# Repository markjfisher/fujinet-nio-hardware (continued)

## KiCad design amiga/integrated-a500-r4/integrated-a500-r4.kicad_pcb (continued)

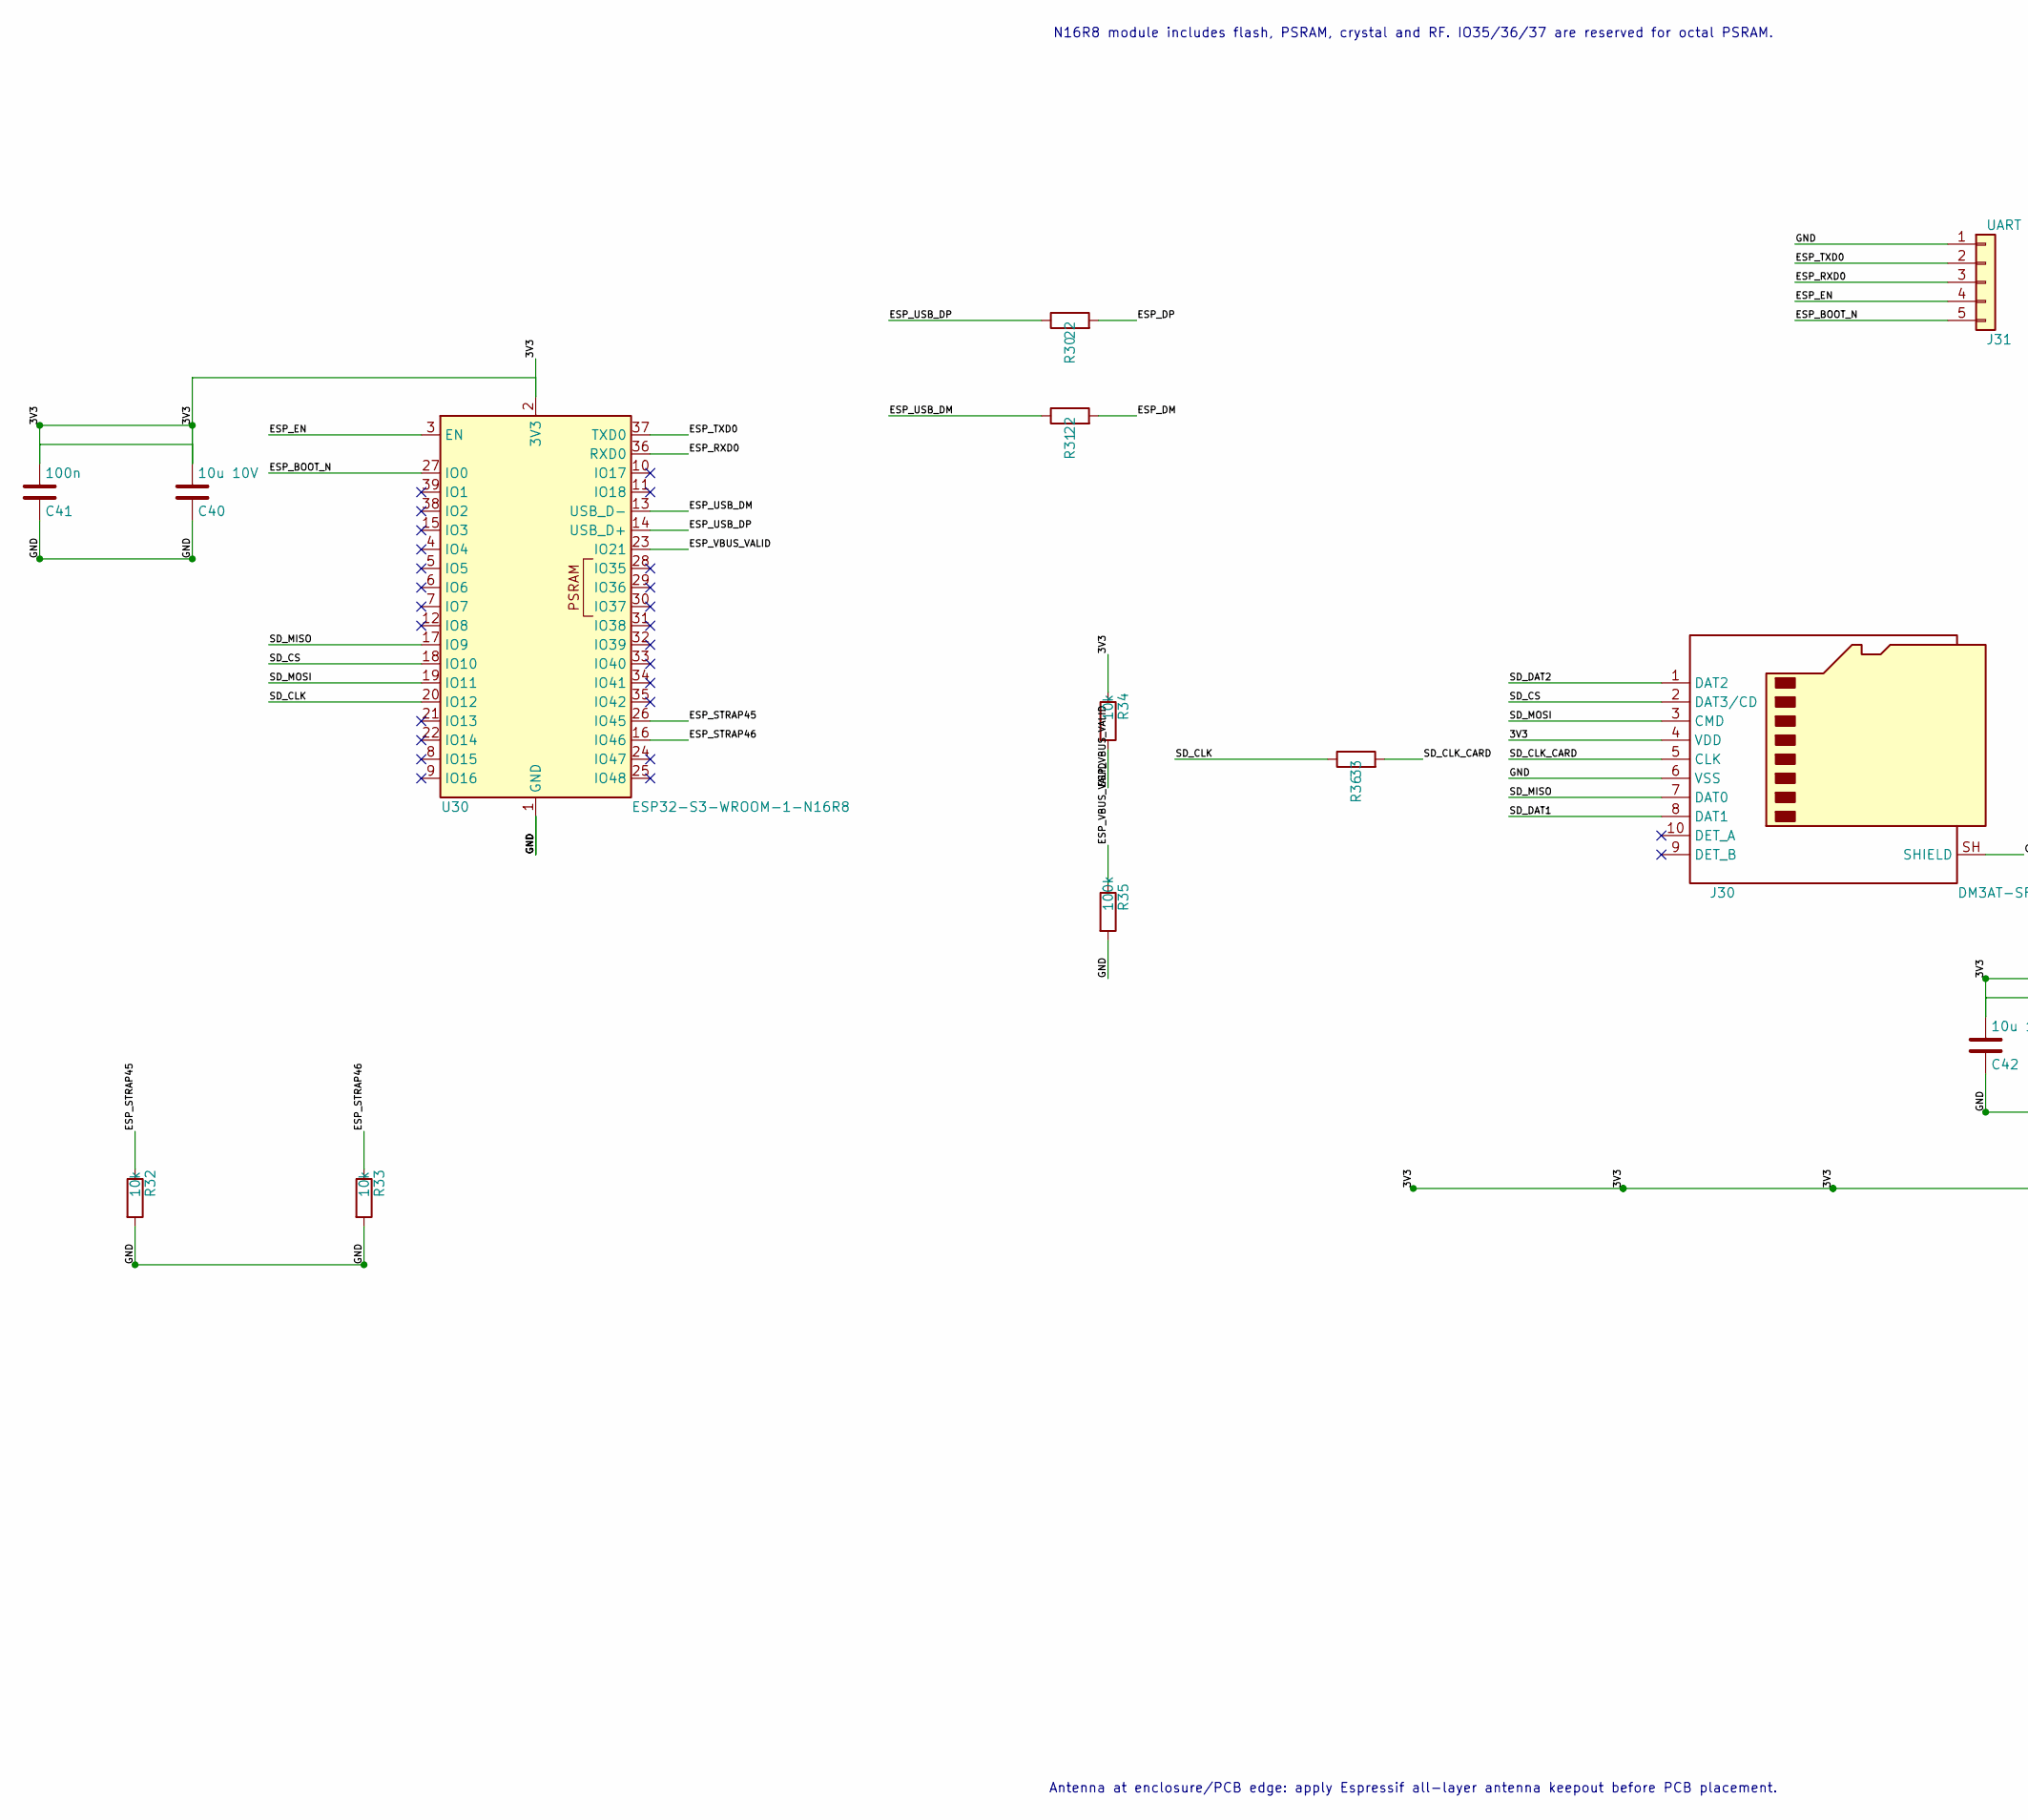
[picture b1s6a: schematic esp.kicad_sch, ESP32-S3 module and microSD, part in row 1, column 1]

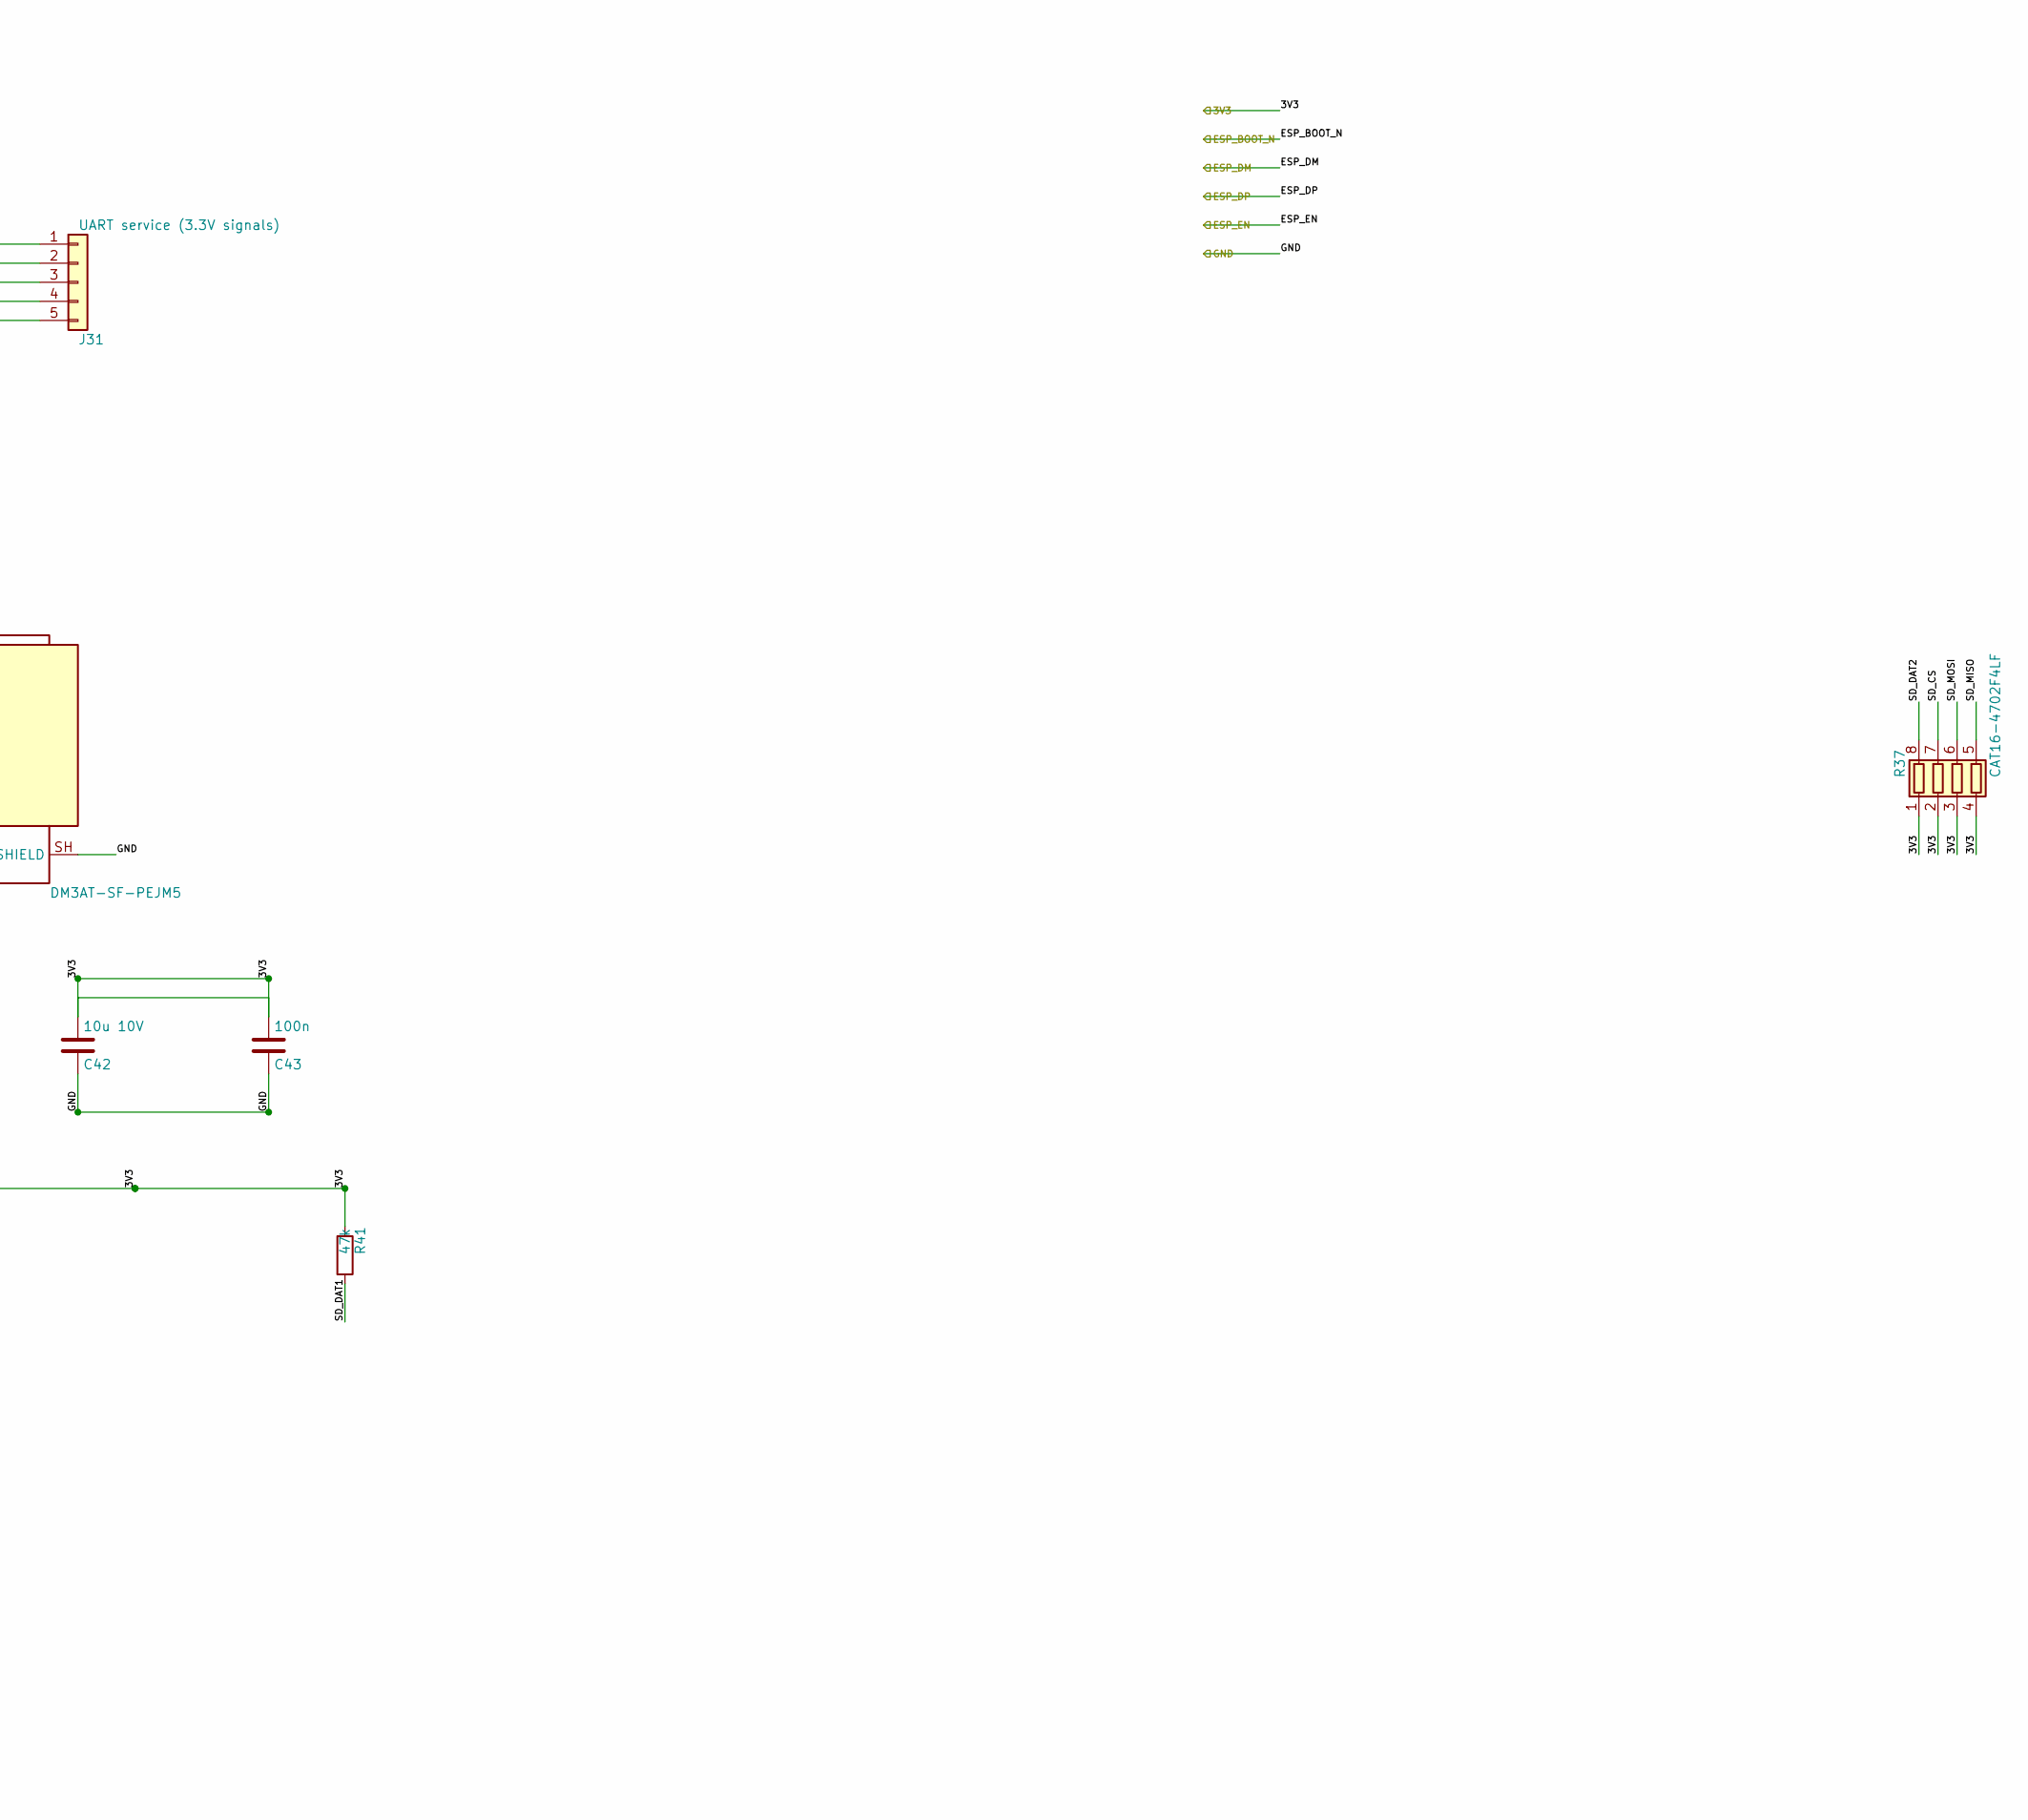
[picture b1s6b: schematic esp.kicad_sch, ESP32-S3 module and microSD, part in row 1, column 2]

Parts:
C40, C42: 10u 10V; C_0603_1608Metric
C41, C43: 100n; C_0603_1608Metric
J30: DM3AT-SF-PEJM5; microSD_HC_Hirose_DM3AT-SF-PEJM5
J31: UART service (3.3V signals); PinHeader_1x05_P2.54mm_Vertical
R30, R31: 22; R_0603_1608Metric
R32, R33, R34: 10k; R_0603_1608Metric
R35: 100k; R_0603_1608Metric
R36: 33; R_0603_1608Metric
R37: CAT16-4702F4LF; R_Array_Concave_4x0603
R41: 47k; R_0603_1608Metric
U30: ESP32-S3-WROOM-1-N16R8; ESP32-S3-WROOM-1

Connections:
/3V3: C40.1, C41.1, C42.1, C43.1, J30.4 (VDD), R34.1, R37.1 (R1.1), R37.2 (R2.1), R37.3 (R3.1), R37.4 (R4.1), R41.1, U30.2 (3V3); also elsewhere on the board
/ESP32-S3 module and microSD/ESP_RXD0: J31.3, U30.36 (RXD0)
/ESP32-S3 module and microSD/ESP_STRAP45: R32.1, U30.26 (IO45)
/ESP32-S3 module and microSD/ESP_STRAP46: R33.1, U30.16 (IO46)
/ESP32-S3 module and microSD/ESP_TXD0: J31.2, U30.37 (TXD0)
/ESP32-S3 module and microSD/ESP_USB_DM: R31.1, U30.13 (USB_D-)
/ESP32-S3 module and microSD/ESP_USB_DP: R30.1, U30.14 (USB_D+)
/ESP32-S3 module and microSD/ESP_VBUS_VALID: R34.2, R35.1, U30.23 (IO21)
/ESP32-S3 module and microSD/SD_CLK: R36.1, U30.20 (IO12)
/ESP32-S3 module and microSD/SD_CLK_CARD: J30.5 (CLK), R36.2
/ESP32-S3 module and microSD/SD_CS: J30.2 (DAT3/CD), R37.7 (R2.2), U30.18 (IO10)
/ESP32-S3 module and microSD/SD_DAT1: J30.8 (DAT1), R41.2
/ESP32-S3 module and microSD/SD_DAT2: J30.1 (DAT2), R37.8 (R1.2)
/ESP32-S3 module and microSD/SD_MISO: J30.7 (DAT0), R37.5 (R4.2), U30.17 (IO9)
/ESP32-S3 module and microSD/SD_MOSI: J30.3 (CMD), R37.6 (R3.2), U30.19 (IO11)
/ESP_BOOT_N: J31.5, U30.27 (IO0); also elsewhere on the board
/ESP_DM: R31.2; also elsewhere on the board
/ESP_DP: R30.2; also elsewhere on the board
/ESP_EN: J31.4, U30.3 (EN); also elsewhere on the board

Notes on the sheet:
N16R8 module includes flash, PSRAM, crystal and RF. IO35/36/37 are reserved for octal PSRAM.
Antenna at enclosure/PCB edge: apply Espressif all-layer antenna keepout before PCB placement.

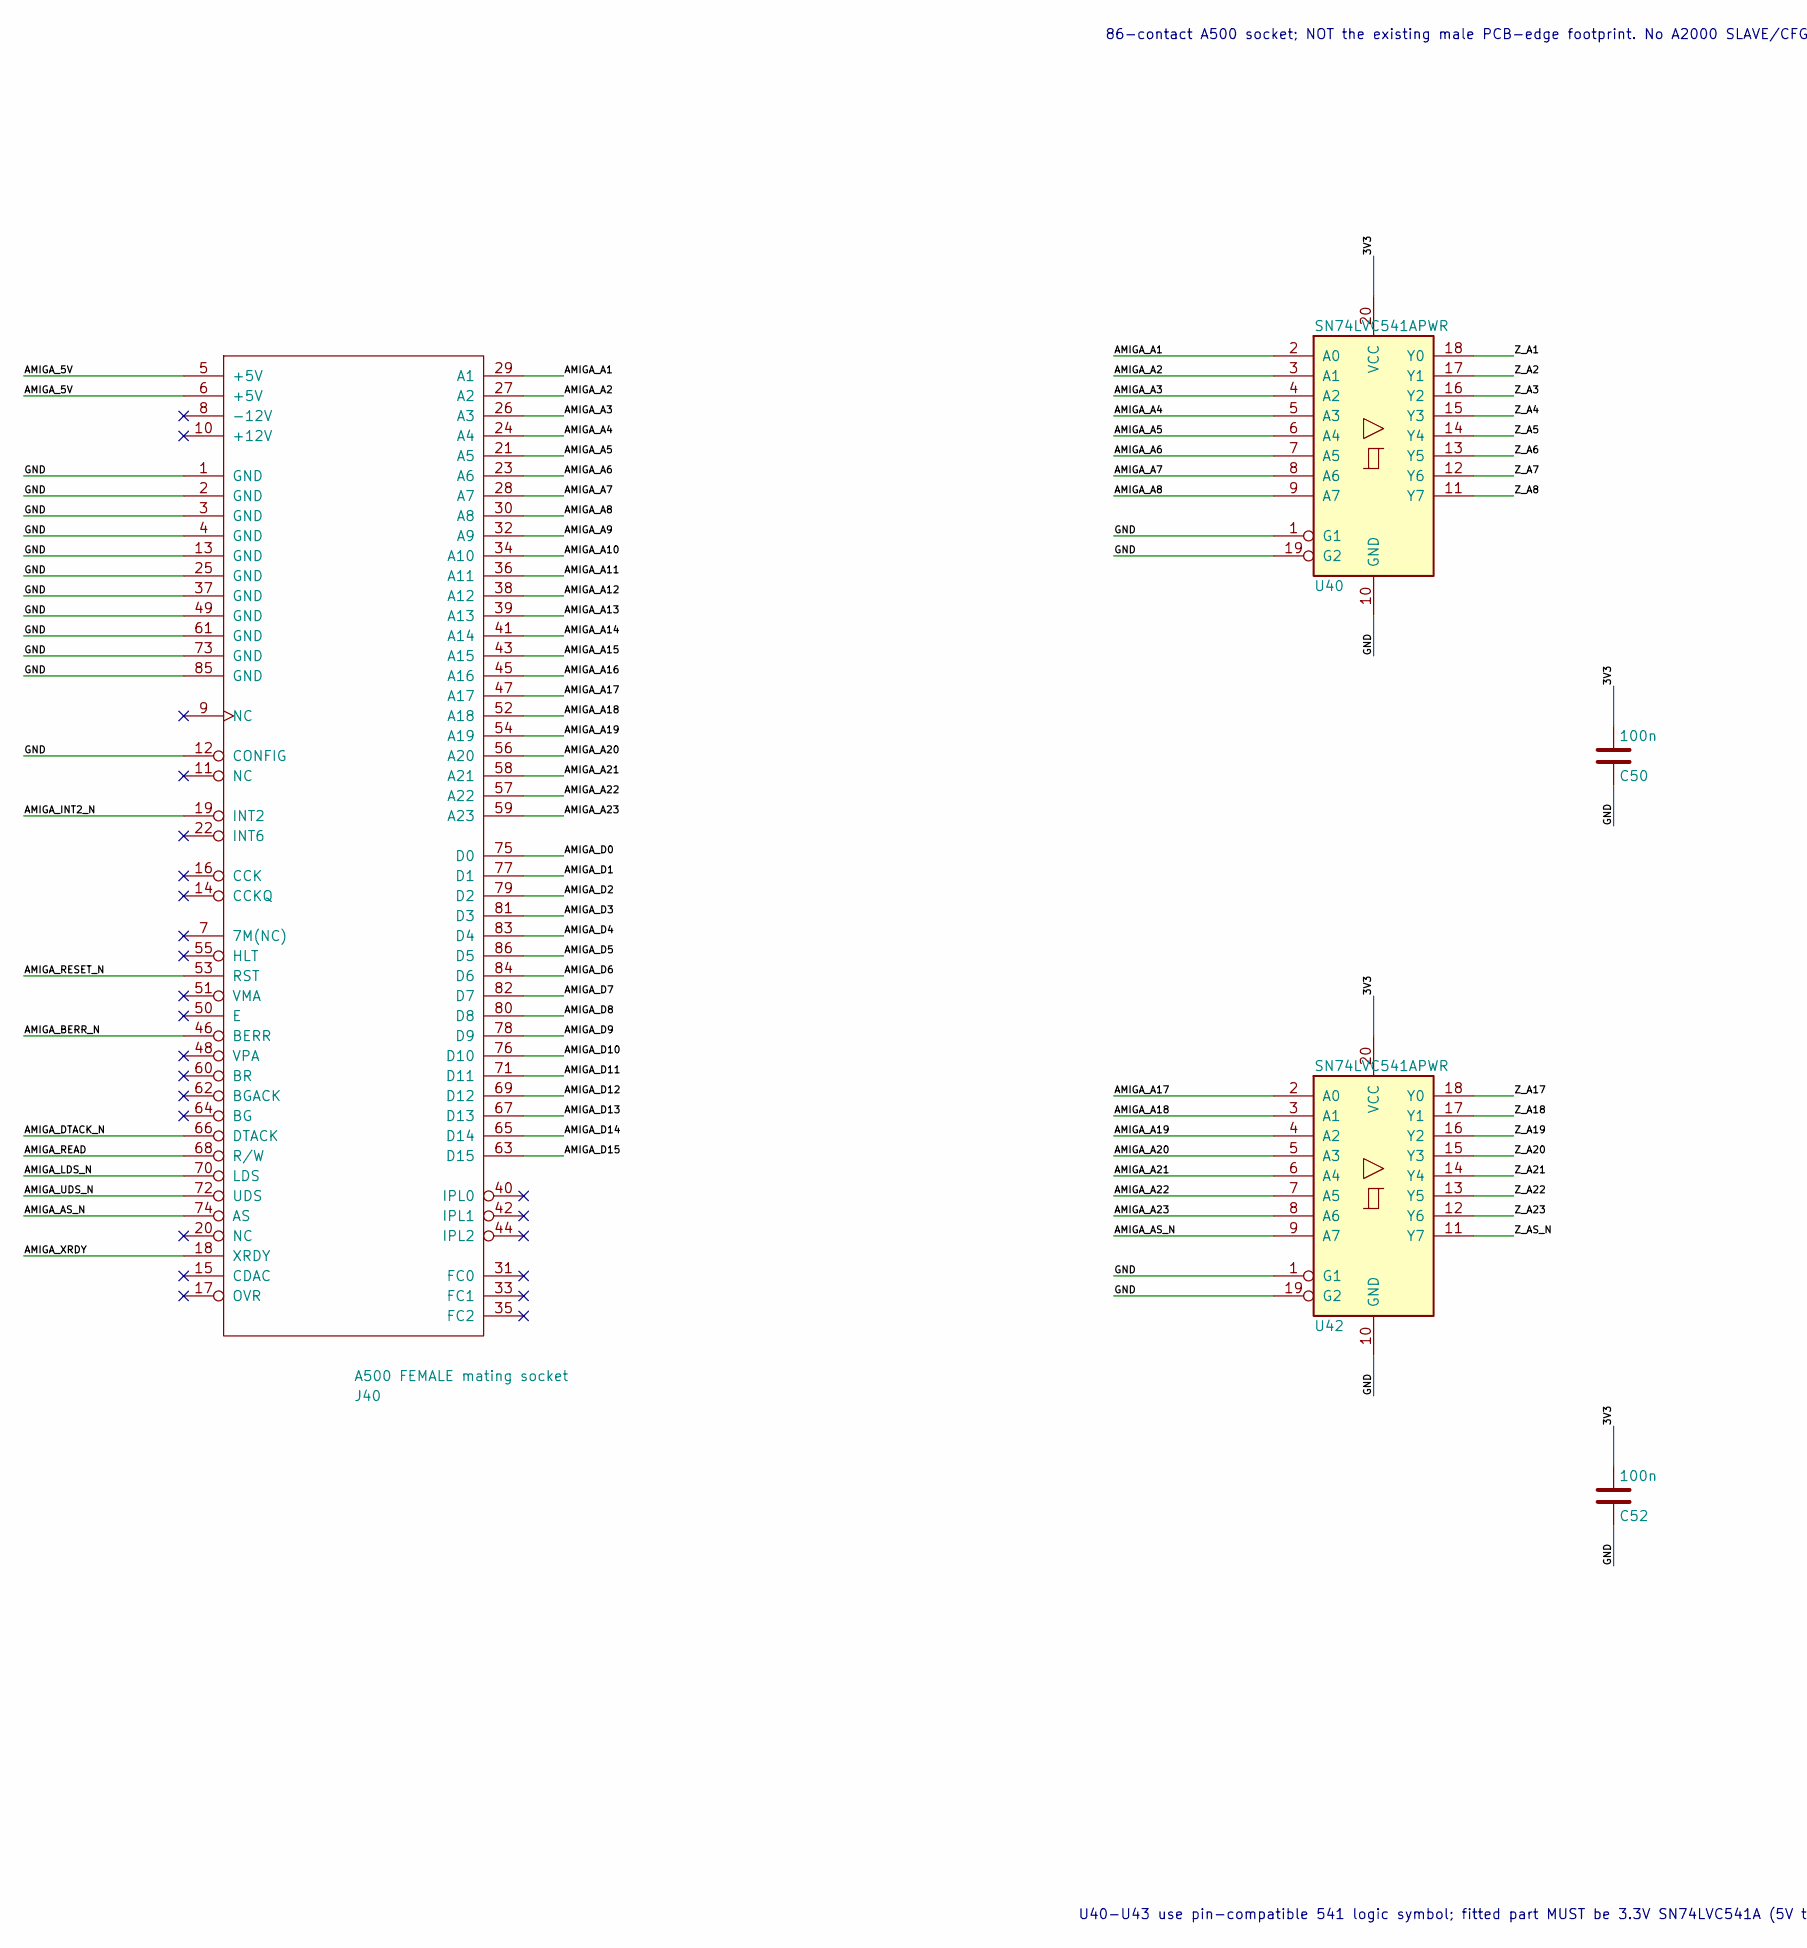
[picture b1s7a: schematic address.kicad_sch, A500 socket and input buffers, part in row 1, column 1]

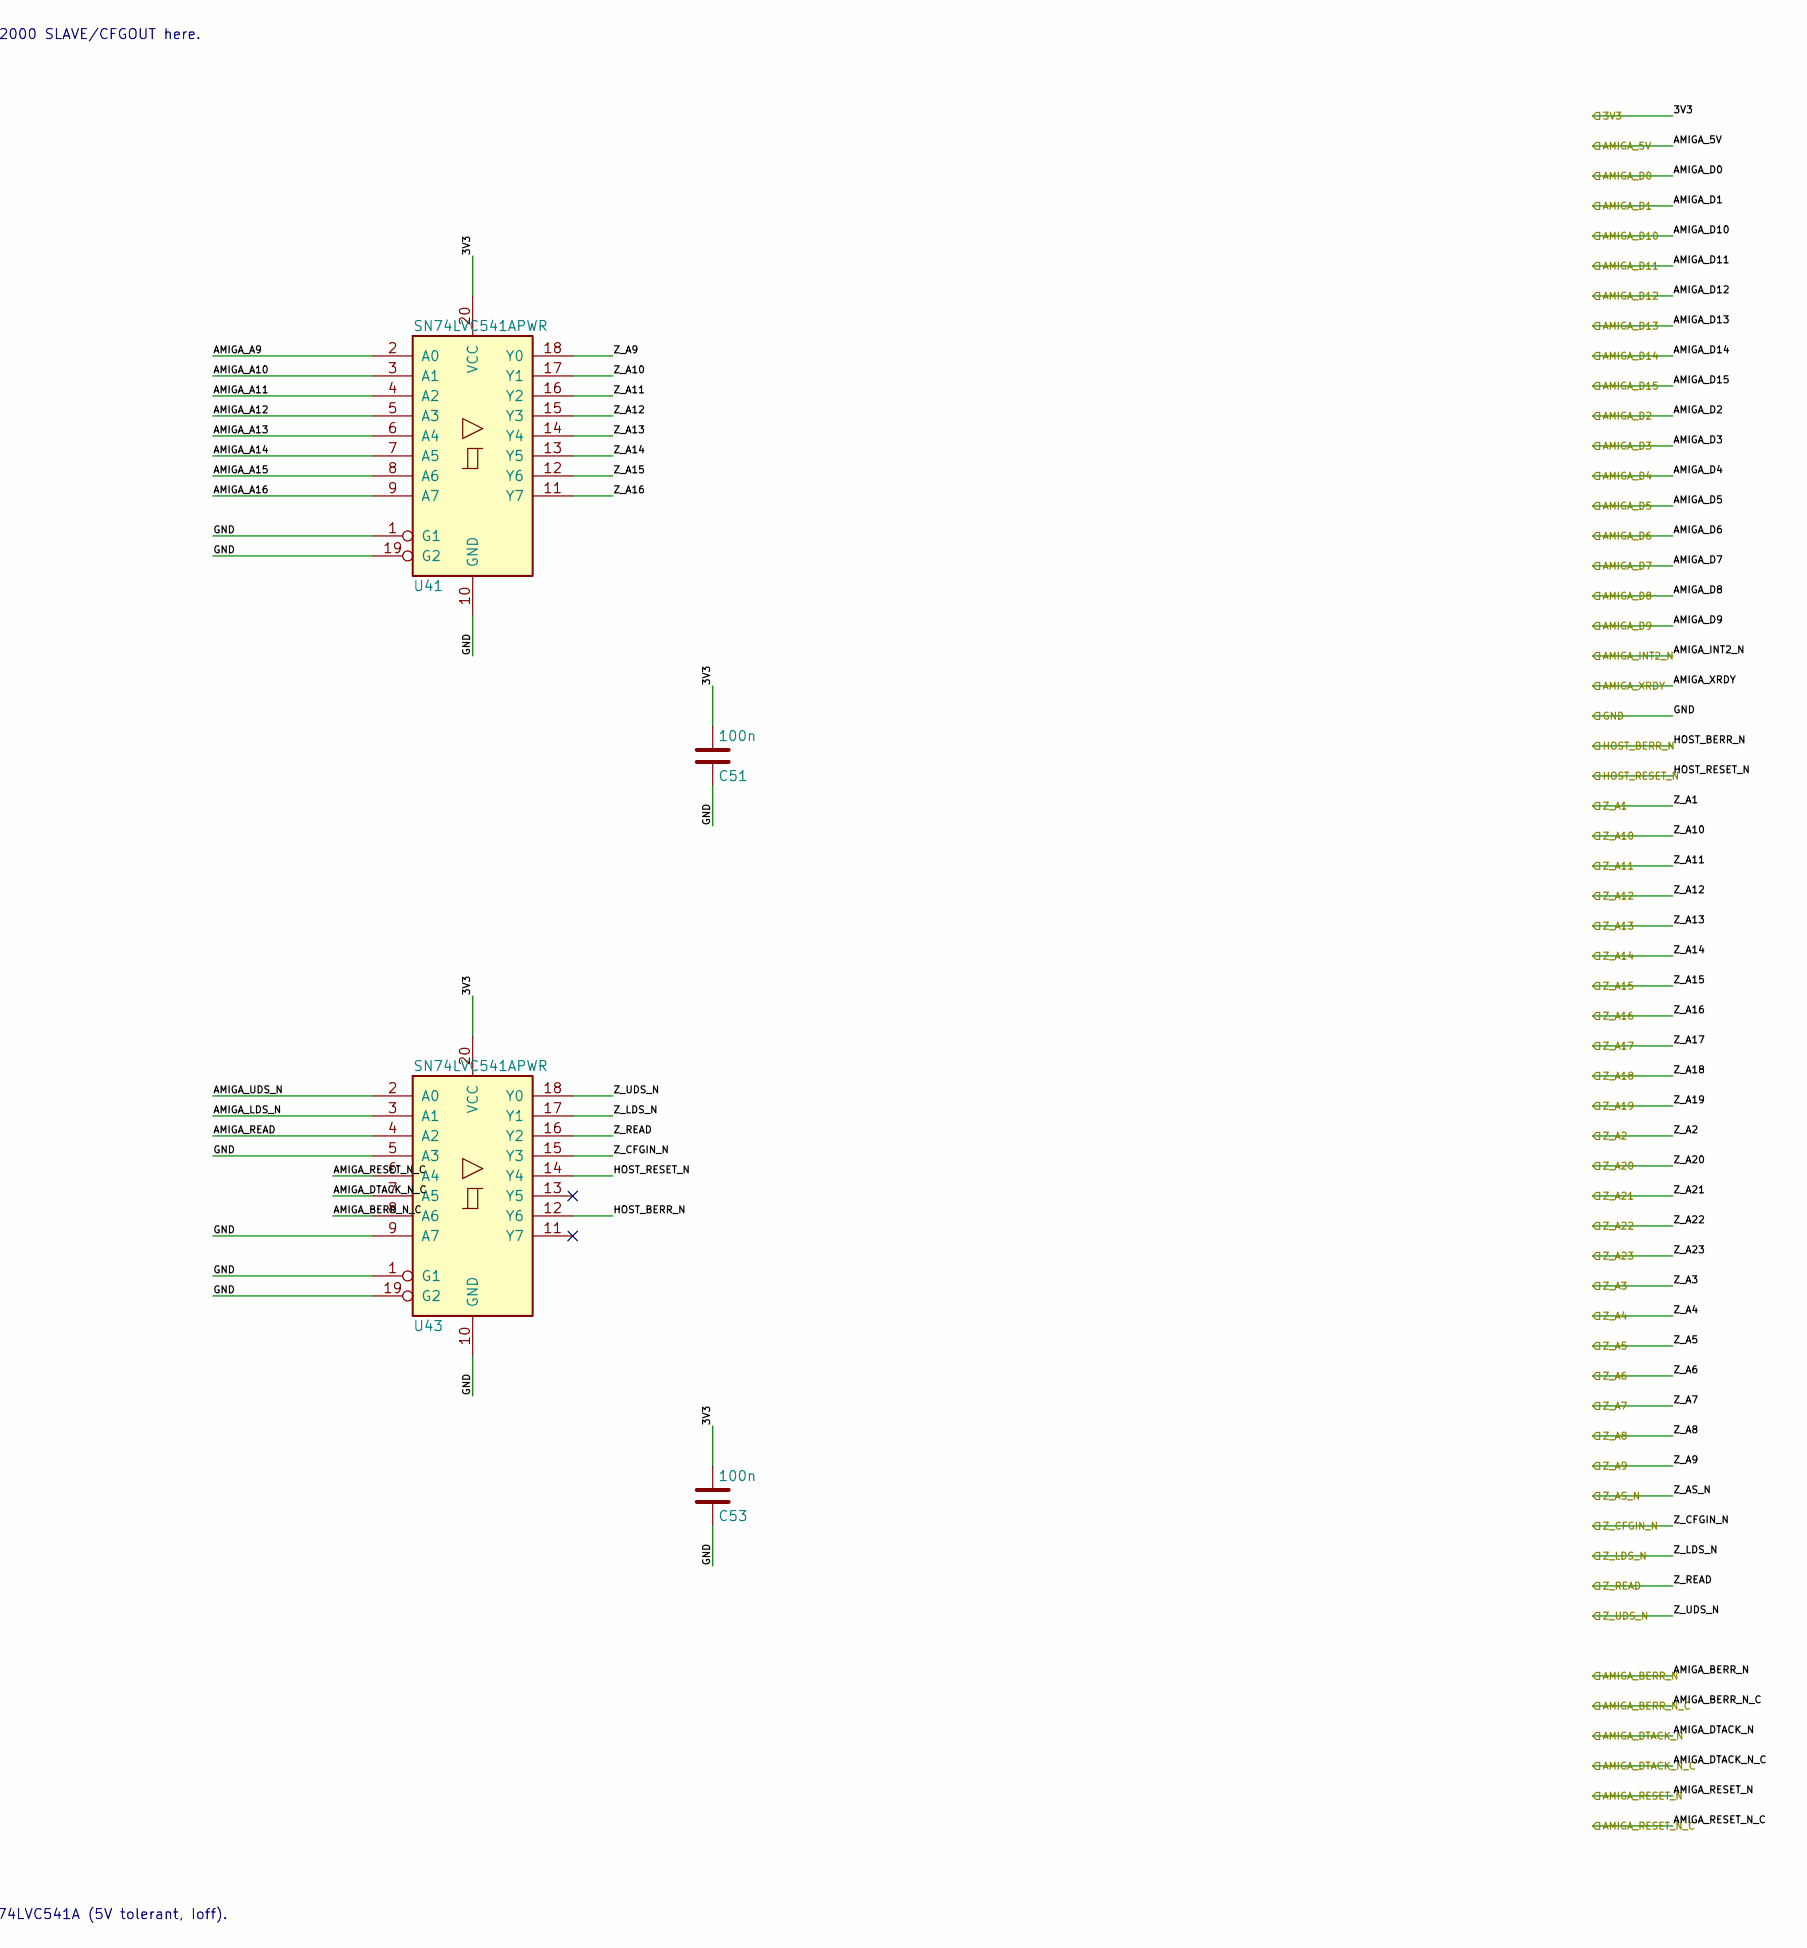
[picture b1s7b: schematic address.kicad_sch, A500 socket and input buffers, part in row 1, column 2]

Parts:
C50, C51, C52, C53: 100n; C_0603_1608Metric
J40: A500 FEMALE mating socket; A500_ED86_EdgeSolder
U40, U41, U42, U43: SN74LVC541APWR; TSSOP-20_4.4x6.5mm_P0.65mm

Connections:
/3V3: C50.1, C51.1, C52.1, C53.1, U40.20 (VCC), U41.20 (VCC), U42.20 (VCC), U43.20 (VCC); also elsewhere on the board
/A500 socket and input buffers/AMIGA_A1: J40.29 (A1), U40.2 (A0)
/A500 socket and input buffers/AMIGA_A2: J40.27 (A2), U40.3 (A1)
/A500 socket and input buffers/AMIGA_A3: J40.26 (A3), U40.4 (A2)
/A500 socket and input buffers/AMIGA_A4: J40.24 (A4), U40.5 (A3)
/A500 socket and input buffers/AMIGA_A5: J40.21 (A5), U40.6 (A4)
/A500 socket and input buffers/AMIGA_A6: J40.23 (A6), U40.7 (A5)
/A500 socket and input buffers/AMIGA_A7: J40.28 (A7), U40.8 (A6)
/A500 socket and input buffers/AMIGA_A8: J40.30 (A8), U40.9 (A7)
/A500 socket and input buffers/AMIGA_A9: J40.32 (A9), U41.2 (A0)
/A500 socket and input buffers/AMIGA_A10: J40.34 (A10), U41.3 (A1)
/A500 socket and input buffers/AMIGA_A11: J40.36 (A11), U41.4 (A2)
/A500 socket and input buffers/AMIGA_A12: J40.38 (A12), U41.5 (A3)
/A500 socket and input buffers/AMIGA_A13: J40.39 (A13), U41.6 (A4)
/A500 socket and input buffers/AMIGA_A14: J40.41 (A14), U41.7 (A5)
/A500 socket and input buffers/AMIGA_A15: J40.43 (A15), U41.8 (A6)
/A500 socket and input buffers/AMIGA_A16: J40.45 (A16), U41.9 (A7)
/A500 socket and input buffers/AMIGA_A17: J40.47 (A17), U42.2 (A0)
/A500 socket and input buffers/AMIGA_A18: J40.52 (A18), U42.3 (A1)
/A500 socket and input buffers/AMIGA_A19: J40.54 (A19), U42.4 (A2)
/A500 socket and input buffers/AMIGA_A20: J40.56 (A20), U42.5 (A3)
/A500 socket and input buffers/AMIGA_A21: J40.58 (A21), U42.6 (A4)
/A500 socket and input buffers/AMIGA_A22: J40.57 (A22), U42.7 (A5)
/A500 socket and input buffers/AMIGA_A23: J40.59 (A23), U42.8 (A6)
/A500 socket and input buffers/AMIGA_AS_N: J40.74 (AS), U42.9 (A7)
/A500 socket and input buffers/AMIGA_LDS_N: J40.70 (LDS), U43.3 (A1)
/A500 socket and input buffers/AMIGA_READ: J40.68 (R/W), U43.4 (A2)
/A500 socket and input buffers/AMIGA_UDS_N: J40.72 (UDS), U43.2 (A0)
/AMIGA_5V: J40.5 (+5V), J40.6 (+5V); also elsewhere on the board
/AMIGA_BERR_N: J40.46 (BERR); also elsewhere on the board
/AMIGA_BERR_N_C: U43.8 (A6); also elsewhere on the board
/AMIGA_D0: J40.75 (D0); also elsewhere on the board
/AMIGA_D1: J40.77 (D1); also elsewhere on the board
/AMIGA_D2: J40.79 (D2); also elsewhere on the board
/AMIGA_D3: J40.81 (D3); also elsewhere on the board
/AMIGA_D4: J40.83 (D4); also elsewhere on the board
/AMIGA_D5: J40.86 (D5); also elsewhere on the board
/AMIGA_D6: J40.84 (D6); also elsewhere on the board
/AMIGA_D7: J40.82 (D7); also elsewhere on the board
/AMIGA_D8: J40.80 (D8); also elsewhere on the board
/AMIGA_D9: J40.78 (D9); also elsewhere on the board
/AMIGA_D10: J40.76 (D10); also elsewhere on the board
/AMIGA_D11: J40.71 (D11); also elsewhere on the board
/AMIGA_D12: J40.69 (D12); also elsewhere on the board
/AMIGA_D13: J40.67 (D13); also elsewhere on the board
/AMIGA_D14: J40.65 (D14); also elsewhere on the board
/AMIGA_D15: J40.63 (D15); also elsewhere on the board
/AMIGA_DTACK_N: J40.66 (DTACK); also elsewhere on the board
/AMIGA_DTACK_N_C: U43.7 (A5); also elsewhere on the board
/AMIGA_INT2_N: J40.19 (INT2); also elsewhere on the board
/AMIGA_RESET_N: J40.53 (RST); also elsewhere on the board
/AMIGA_RESET_N_C: U43.6 (A4); also elsewhere on the board
/AMIGA_XRDY: J40.18 (XRDY); also elsewhere on the board
/HOST_BERR_N: U43.12 (Y6); also elsewhere on the board
/HOST_RESET_N: U43.14 (Y4); also elsewhere on the board
/Z_A1: U40.18 (Y0); also elsewhere on the board
/Z_A2: U40.17 (Y1); also elsewhere on the board
/Z_A3: U40.16 (Y2); also elsewhere on the board
/Z_A4: U40.15 (Y3); also elsewhere on the board
/Z_A5: U40.14 (Y4); also elsewhere on the board
/Z_A6: U40.13 (Y5); also elsewhere on the board
/Z_A7: U40.12 (Y6); also elsewhere on the board
/Z_A8: U40.11 (Y7); also elsewhere on the board
/Z_A9: U41.18 (Y0); also elsewhere on the board
/Z_A10: U41.17 (Y1); also elsewhere on the board
/Z_A11: U41.16 (Y2); also elsewhere on the board
/Z_A12: U41.15 (Y3); also elsewhere on the board
/Z_A13: U41.14 (Y4); also elsewhere on the board
/Z_A14: U41.13 (Y5); also elsewhere on the board
/Z_A15: U41.12 (Y6); also elsewhere on the board
/Z_A16: U41.11 (Y7); also elsewhere on the board
/Z_A17: U42.18 (Y0); also elsewhere on the board
/Z_A18: U42.17 (Y1); also elsewhere on the board
/Z_A19: U42.16 (Y2); also elsewhere on the board
/Z_A20: U42.15 (Y3); also elsewhere on the board
/Z_A21: U42.14 (Y4); also elsewhere on the board
/Z_A22: U42.13 (Y5); also elsewhere on the board
/Z_A23: U42.12 (Y6); also elsewhere on the board
/Z_AS_N: U42.11 (Y7); also elsewhere on the board
/Z_CFGIN_N: U43.15 (Y3); also elsewhere on the board
/Z_LDS_N: U43.17 (Y1); also elsewhere on the board
/Z_READ: U43.16 (Y2); also elsewhere on the board
/Z_UDS_N: U43.18 (Y0); also elsewhere on the board

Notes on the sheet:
86-contact A500 socket; NOT the existing male PCB-edge footprint. No A2000 SLAVE/CFGOUT here.
U40-U43 use pin-compatible 541 logic symbol; fitted part MUST be 3.3V SN74LVC541A (5V tolerant, Ioff).
